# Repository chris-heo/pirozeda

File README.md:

# Pirozeda

This is the official repo of the Pirozeda project hosted on [hobbyelektronik.org](https://hobbyelektronik.org/w/index.php/Pirozeda).

This hard- and software enables you to capture and record data from a Prozeda heating controller with a Raspberry Pi.

Please note that both the server backend and frontend is more intended to ba a demonstrator and does not represent a proper software design.

Read more about it in the above linked documentation (German only).

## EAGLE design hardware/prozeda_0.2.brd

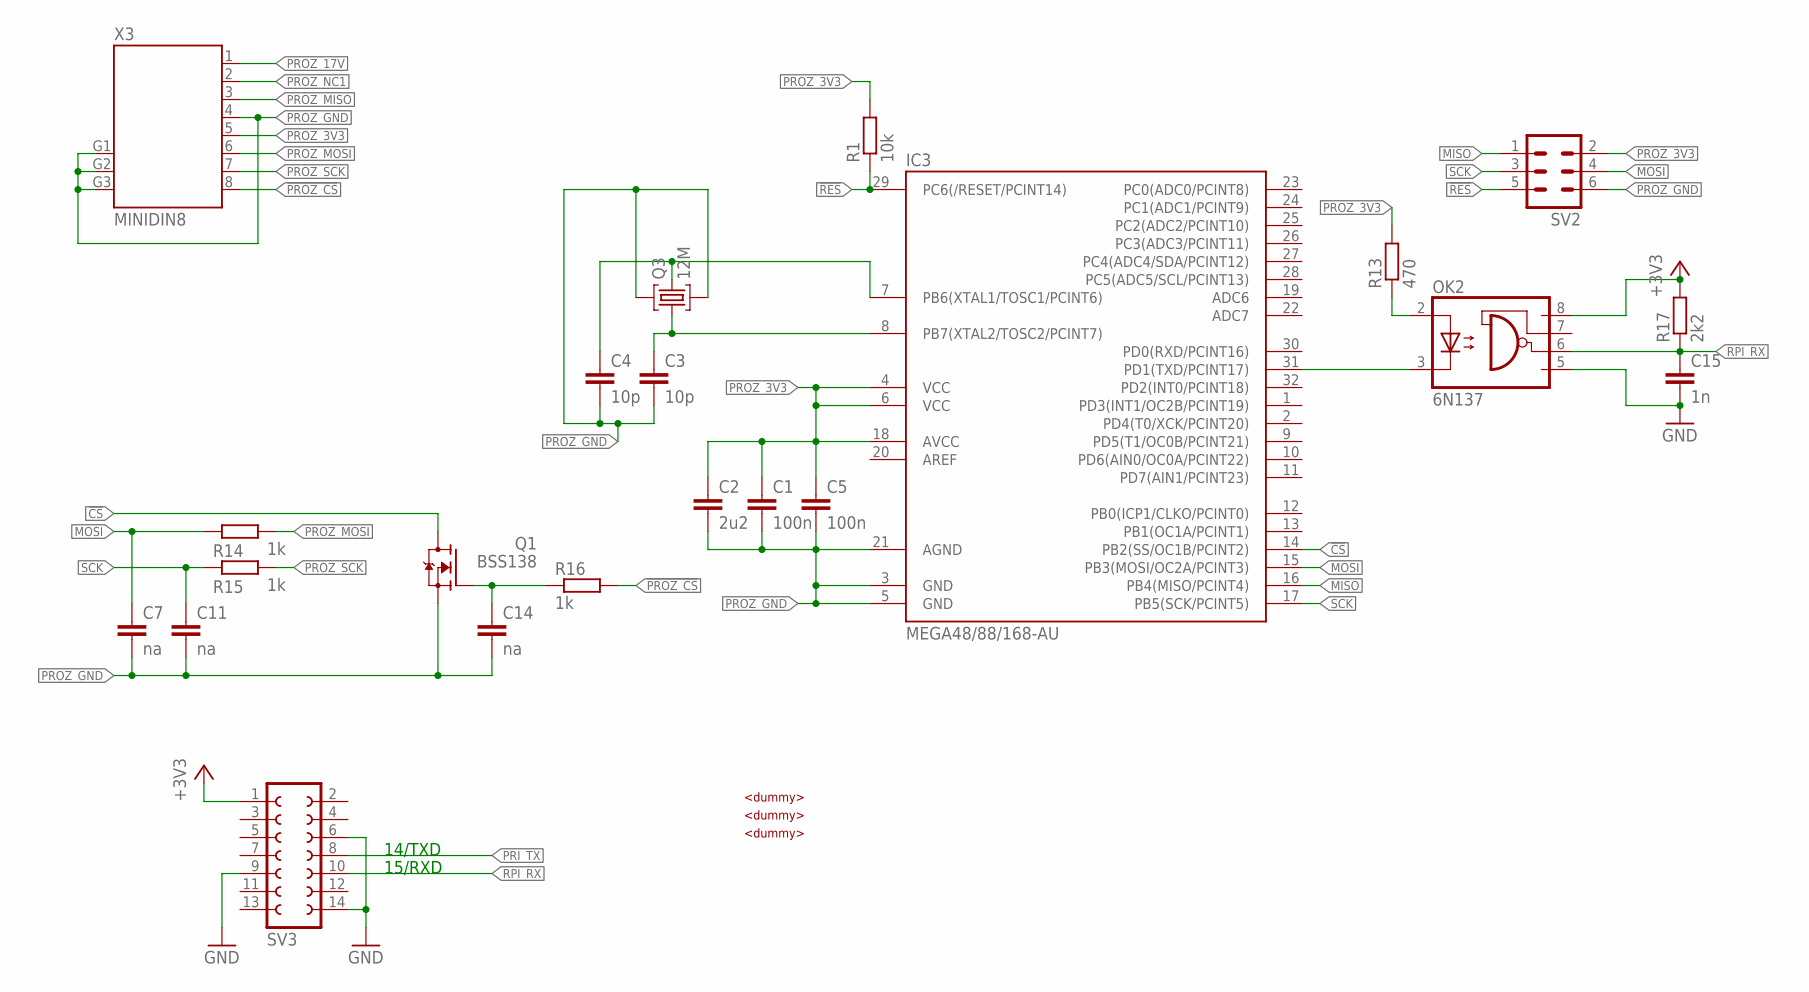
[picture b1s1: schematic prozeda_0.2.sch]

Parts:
C1, C5: 100n; C0603
C2: 2u2; C0805
C3, C4: 10p; C0603
C7, C11, C14: na; C0603
C15: 1n; C0603
IC3: MEGA48/88/168-AU; TQFP32-08
OK2: 6N137; DIL08
Q1: BSS138; SOT23
Q3: 12M; MJ
R1: 10k; R0603
R13: 470; R0603
R14, R15, R16: 1k; R0603
R17: 2k2; R0603
SV2: MA03-2
SV3: FE07-2
U$1, U$2, U$3: DUMMY
X3: MINIDIN8; MINI-DIN8

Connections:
!CS: IC3.14 (PB2(SS/OC1B/PCINT2)), Q1.3 (D)
!PROZ_CS: R16.2, X3.8
!RES: IC3.29 (PC6(/RESET/PCINT14)), R1.1, SV2.5
+3V3: OK2.8 (VCC), R17.2, SV3.1
GND: C15.2, OK2.5 (GND), SV3.6, SV3.9, SV3.14
MISO: IC3.16 (PB4(MISO/PCINT4)), SV2.1
MOSI: C7.1, IC3.15 (PB3(MOSI/OC2A/PCINT3)), R14.1, SV2.4
unnamed: C3.1, IC3.8 (PB7(XTAL2/TOSC2/PCINT7)), Q3.1
unnamed: C4.1, IC3.7 (PB6(XTAL1/TOSC1/PCINT6)), Q3.3
unnamed: C14.1, Q1.1 (G), R16.1
unnamed: IC3.31 (PD1(TXD/PCINT17)), OK2.3 (C)
unnamed: OK2.2 (A), R13.1
PRI_TX: SV3.8
PROZ_3V3: C1.1, C2.1, C5.1, IC3.4 (VCC), IC3.6 (VCC), IC3.18 (AVCC), R1.2, R13.2, SV2.2, X3.5
PROZ_17V: X3.1
PROZ_GND: C1.2, C2.2, C3.2, C4.2, C5.2, C7.2, C11.2, C14.2, IC3.3 (GND), IC3.5 (GND), IC3.21 (AGND), Q1.2 (S), Q3.2, Q3.4, SV2.6, X3.4, X3.G1, X3.G2, X3.G3
PROZ_MISO: X3.3
PROZ_MOSI: R14.2, X3.6
PROZ_NC1: X3.2
PROZ_SCK: R15.2, X3.7
RPI_RX: C15.1, OK2.6 (VO), R17.1, SV3.10
SCK: C11.1, IC3.17 (PB5(SCK/PCINT5)), R15.1, SV2.3

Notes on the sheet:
14/TXD
15/RXD

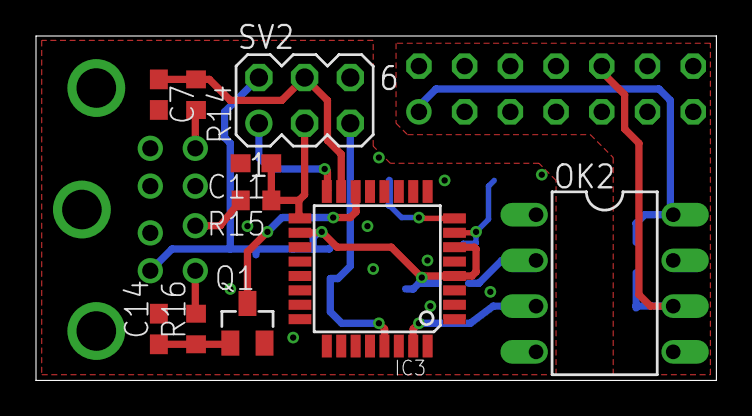
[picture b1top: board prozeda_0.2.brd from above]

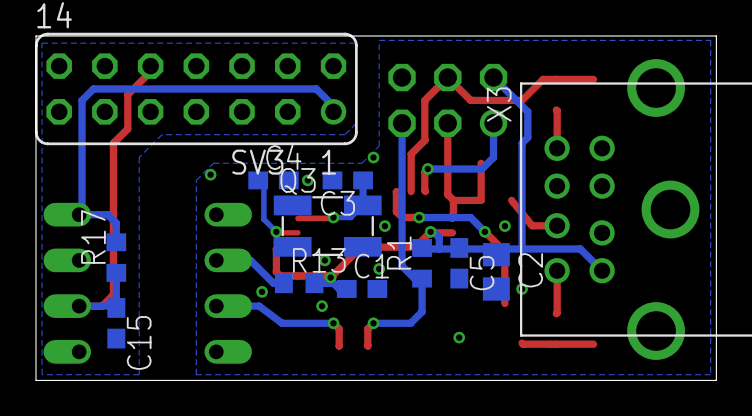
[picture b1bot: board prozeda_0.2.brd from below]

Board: 2 copper layers, 37.8 x 19.1 mm, 25 parts (12 on the bottom side), 18 nets.

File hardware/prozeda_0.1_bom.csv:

"Qty";"Value";"Device";"Package";"Parts";"Description";"MF";"MPN";"OC_FARNELL";"OC_NEWARK";"OC_REICHELT";
"1";"";"FE07-2";"FE07-2";"SV3";"FEMALE HEADER";"";"";"";"";"";
"1";"";"MA03-2";"MA03-2";"SV2";"PIN HEADER";"";"";"unknown";"unknown";"";
"2";"100n";"C-EUC0603";"C0603";"C1, C5";"CAPACITOR, European symbol";"";"";"";"";"X7R-G0603 100N";
"1";"10k";"R-EU_R0603";"R0603";"R1";"RESISTOR, European symbol";"";"";"";"";"RND 0603 1 10K";
"2";"10p";"C-EUC0603";"C0603";"C3, C4";"CAPACITOR, European symbol";"";"";"";"";"X7R-G0603 10p";
"1";"12M";"SMD4PADMJ";"MJ";"Q3";"";"";"";"";"";"12,000000-MJ";
"3";"1k";"R-EU_R0603";"R0603";"R14, R15, R16";"RESISTOR, European symbol";"";"";"";"";"RND 0603 1 1K";
"1";"1n";"C-EUC0603";"C0603";"C15";"CAPACITOR, European symbol";"";"";"";"";"X7R-G0603 1np";
"1";"2k2";"R-EU_R0603";"R0603";"R17";"RESISTOR, European symbol";"";"";"";"";"RND 0603 1 2,2K";
"1";"2u2";"C-EUC0805";"C0805";"C2";"CAPACITOR, European symbol";"";"";"";"";"KEM X5R0805 2,2U";
"1";"470";"R-EU_R0603";"R0603";"R13";"RESISTOR, European symbol";"";"";"";"";"RND 0603 1 470";
"1";"6N137";"6N137";"DIL08";"OK2";"MOTOROLA OPTO COUPLER";"";"6N137";"1328376";"52M1895";"6N 137";
"1";"BSS138";"BSS138";"SOT23";"Q1";"";"";"";"9845330";"";"BSS 138 SMD";
"1";"DUMMY";"DUMMY";"DUMMY";"U$1";"";"";"";"";"";"EB-DIO M08";
"2";"DUMMY";"DUMMY";"DUMMY";"U$2, U$3";"";"";"";"";"";"SE-DIO M08";
"1";"MEGA48/88/168-AU";"MEGA48/88/168-AU";"TQFP32-08";"IC3";"";"";"";"";"";"ATMEGA 88PA-AU";
"1";"MINIDIN8";"MINIDIN8";"MINI-DIN8";"X3";"";"";"";"";"";"EB-DIOS M08";
"3";"na";"C-EUC0603";"C0603";"C7, C11, C14";"CAPACITOR, European symbol";"";"";"";"";"X7R-G0603 220p";

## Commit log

2018-08-27 Importierte Ordnerstruktur
2018-08-27 * First non-public PoC
2018-08-27 * First public release
2018-08-27 * Fixed wrong display of Storage [kWh], Storage [h], Flowrate [l/min] * Fixed timing issue in firmware with displaydata-messages on some controllers * Disabled printing log messages of pyjsonrpc's ht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
2018-08-27 * Fixed issue where both current + displaydata and stats aren't updated This is due to the inserted 3D-diagram which wasn't taken into account of loading/updating the data context sensitive
2021-02-22 added README.md and LICENSE.md
2022-10-08 version bump to 0.4 (how could I forget this?)
2022-10-08 added requirements.txt
2022-10-31 Python backend: added logging & settings for logging added info how long no data was received
2022-10-31 added config file for central backend server config added simple logging (mainly for performance measurements) everything is pretty much untested
2022-11-06 fixed regression: conversion of string to list of int not required
2022-11-06 removed unnecessary requirement in requirements.txt
2022-11-06 added global handler to log exception added memory usage logger to find memory hogs moved logfile location to pirozeda_settings.py changed and added some comments to prozedadisplay.py
2022-11-06 added global handler to log exception added memory usage logger to find memory hogs moved logfile location to pirozeda_settings.py changed and added some comments to prozedadisplay.py added settings 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
2022-11-12 fixed: only first message in session was written to the logfile
